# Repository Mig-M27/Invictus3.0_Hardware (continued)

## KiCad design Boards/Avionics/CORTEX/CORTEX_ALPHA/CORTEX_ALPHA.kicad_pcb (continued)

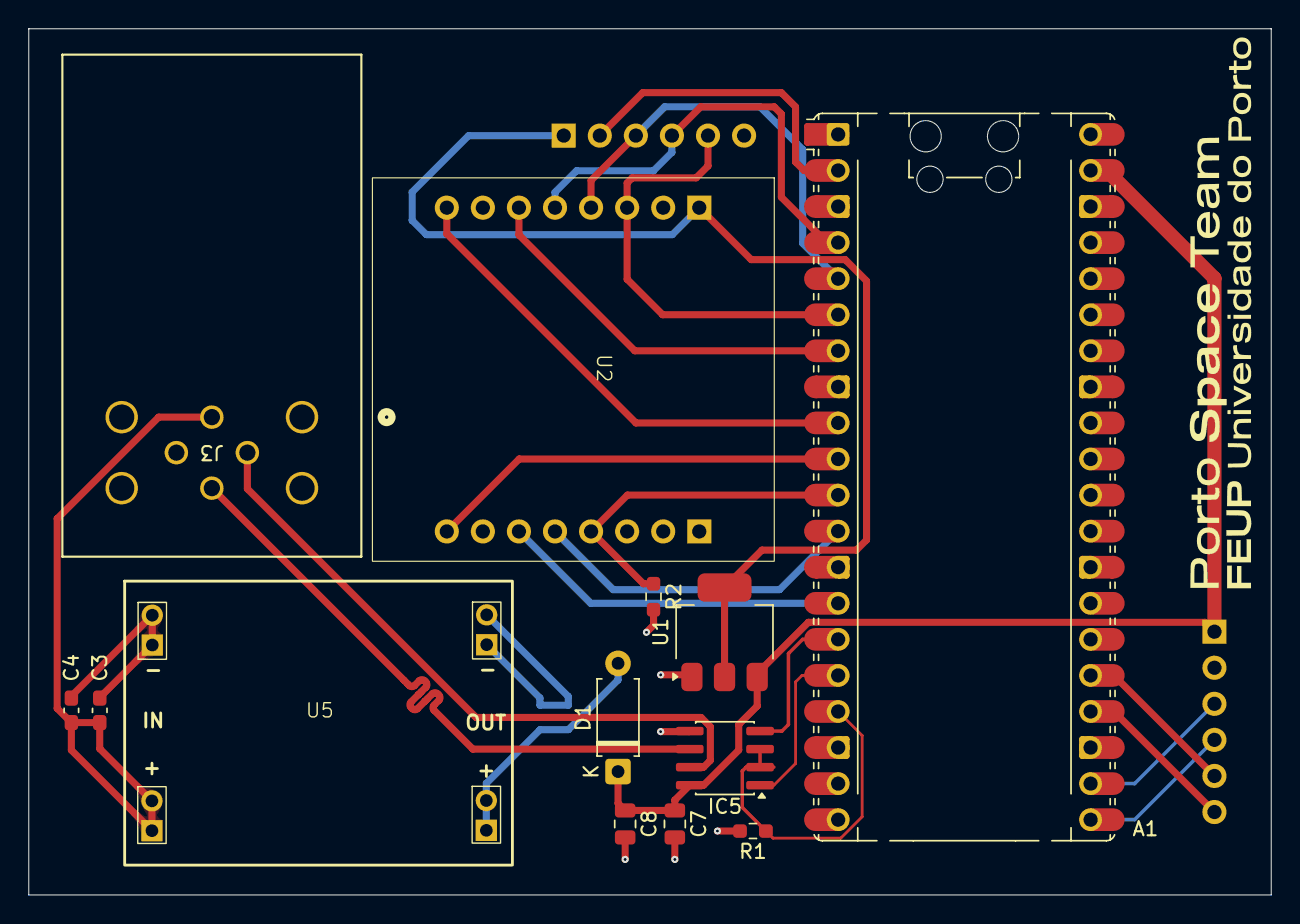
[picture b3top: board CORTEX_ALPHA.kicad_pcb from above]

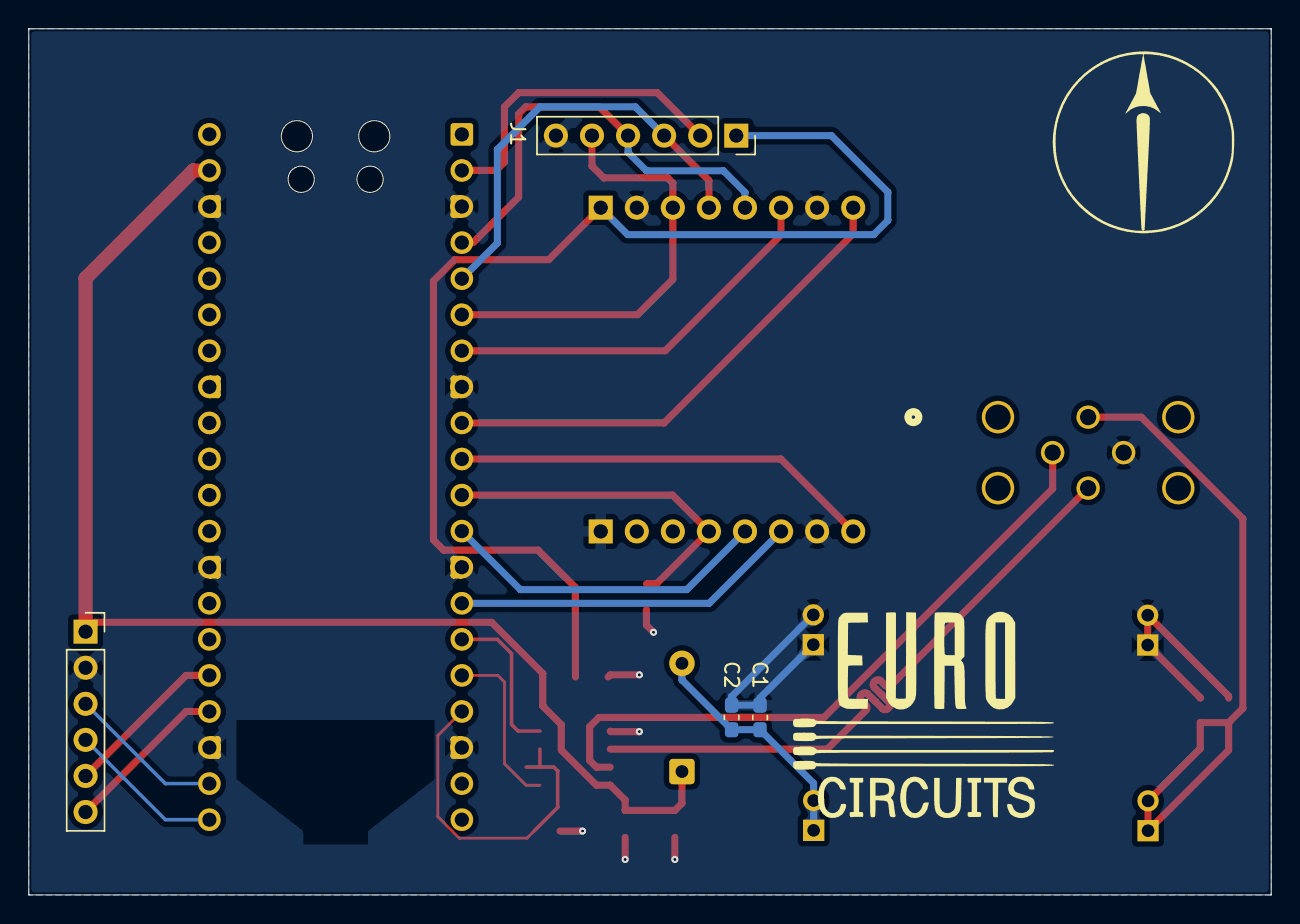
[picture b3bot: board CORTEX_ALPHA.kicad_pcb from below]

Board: 2 copper layers, 87.5 x 61.0 mm, 17 parts (4 on the bottom side), 24 nets.

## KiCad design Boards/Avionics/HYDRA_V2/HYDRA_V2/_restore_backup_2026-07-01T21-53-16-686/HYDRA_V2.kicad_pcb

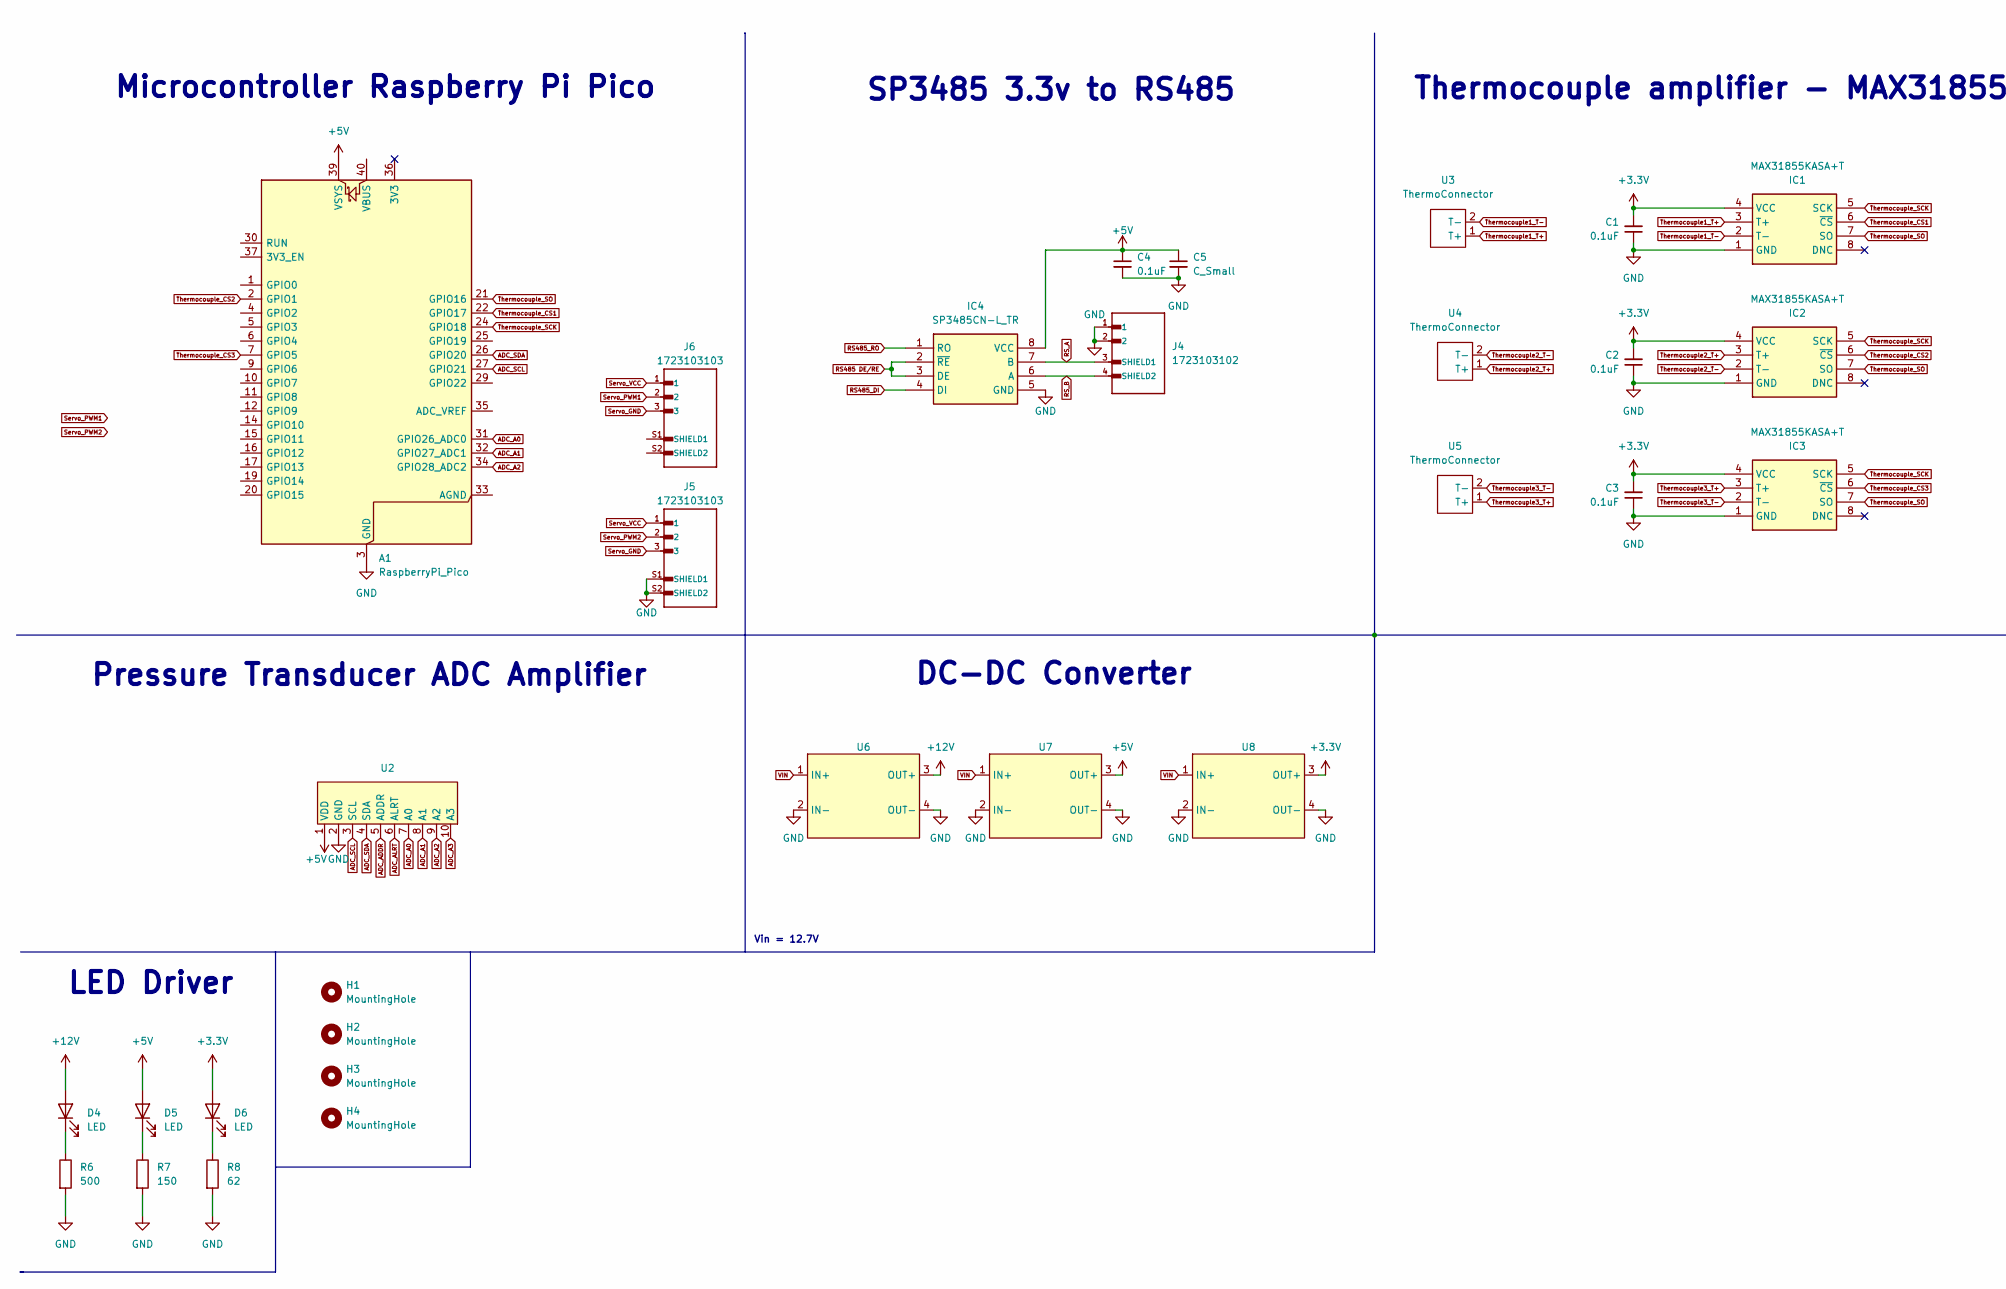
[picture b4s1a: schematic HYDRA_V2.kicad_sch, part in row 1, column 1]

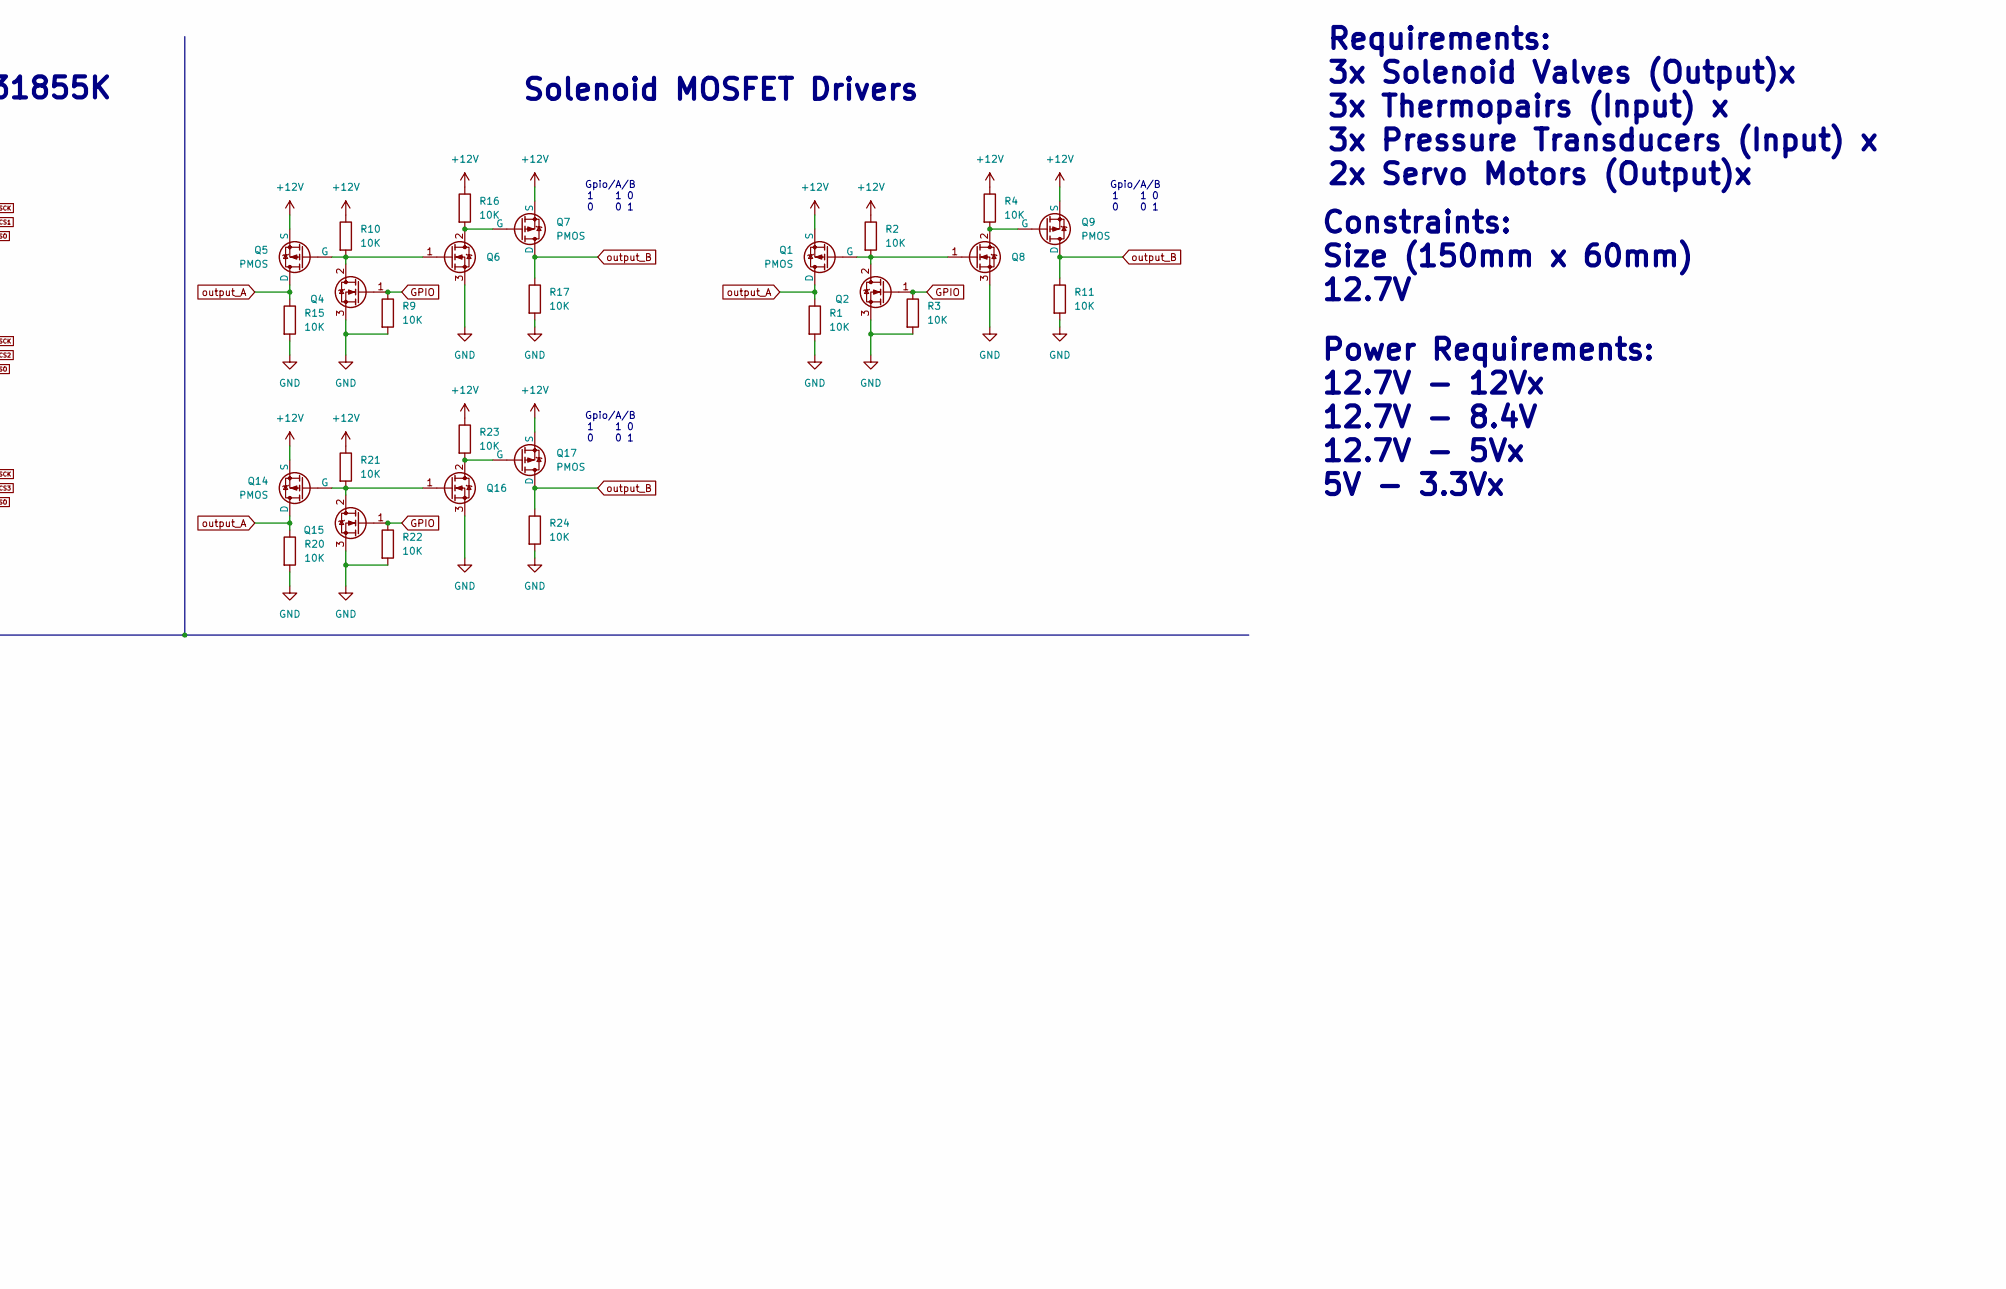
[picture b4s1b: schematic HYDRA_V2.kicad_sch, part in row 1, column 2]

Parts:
A1: RaspberryPi_Pico; RaspberryPi_Pico_Common_Unspecified
C1, C2, C3, C4: 0.1uF; C_0805_2012Metric
C5: C_Small; C_0805_2012Metric
D4, D5, D6: LED; LED_D3.0mm
H1, H2, H3, H4: MountingHole; MountingHole_3.2mm_M3_ISO7380
IC1, IC2, IC3: MAX31855KASA+T; SOIC127P600X175-8N; Mouser Part Number 700-MAX31855KASA+T
IC4: SP3485CN-L_TR; SOIC127P600X175-8N; Mouser Part Number 701-SP3485CN-L/TR
J4: 1723103102; CONN02_1723103102_MOL; MANUFACTURER_PART_NUMBER 1723103102; DigiKey_Part_Number 900-1723103102-ND
J5, J6: 1723103103; MOLEX_1723103103; PARTREV B1; DigiKey_Part_Number 900-1723103103-ND
Q1, Q5, Q7, Q9, Q14, Q17: PMOS; TO-220-3_Vertical
Q2, Q4, Q6, Q8, Q15, Q16: IRLB3813PBF-ND; TO-220-3_Vertical
R1, R2, R3, R4, R9, R10, R11, R15, R16, R17, R20, R21, R22, R23, R24: 10K; R_0805_2012Metric_Pad1.20x1.40mm_HandSolder
R6: 500; R_0805_2012Metric
R7: 150; R_0805_2012Metric
R8: 62; R_0805_2012Metric
U2: Pressure_Amp
U3, U4, U5: ThermoConnector; Thermo Type K PCB Connector
U6, U7, U8: DCDC_Module

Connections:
+3.3V: C1.2, C2.2, C3.2, D6.2 (A), IC1.4 (VCC), IC2.4 (VCC), IC3.4 (VCC), U8.3 (OUT+)
+5V: A1.39 (VSYS), C4.1, C5.1, D5.2 (A), IC4.8 (VCC), U2.1 (VDD), U7.3 (OUT+)
+12V: D4.2 (A), Q1.3 (S), Q5.3 (S), Q7.3 (S), Q9.3 (S), Q14.3 (S), Q17.3 (S), R2.1, R4.1, R10.1, R16.1, R21.1, R23.1, U6.3 (OUT+)
ADC_A0: A1.31 (GPIO26_ADC0), U2.7 (A0)
ADC_A1: A1.32 (GPIO27_ADC1), U2.8 (A1)
ADC_A2: A1.34 (GPIO28_ADC2), U2.9 (A2)
ADC_A3: U2.10 (A3)
ADC_ADDR: U2.5 (ADDR)
ADC_ALRT: U2.6 (ALRT)
ADC_SCL: A1.27 (GPIO21), U2.3 (SCL)
ADC_SDA: A1.26 (GPIO20), U2.4 (SDA)
GND: A1.3 (GND), A1.8 (GND), A1.13 (GND), A1.18 (GND), A1.23 (GND), A1.28 (GND), A1.38 (GND), C1.1, C2.1, C3.1, C4.2, C5.2, IC1.1 (GND), IC2.1 (GND), IC3.1 (GND), IC4.5 (GND), J4.1, J4.2, J5.S1 (SHIELD1), J5.S2 (SHIELD2), Q2.3 (S), Q4.3 (S), Q6.3 (S), Q8.3 (S), Q15.3 (S), Q16.3 (S), R1.2, R3.2, R6.2, R7.2, R8.2, R9.2, R11.2, R15.2, R17.2, R20.2, R22.2, R24.2, U2.2 (GND), U6.2 (IN-), U6.4 (OUT-), U7.2 (IN-), U7.4 (OUT-), U8.2 (IN-), U8.4 (OUT-)
GPIO: Q2.1 (G), Q4.1 (G), Q15.1 (G), R3.1, R9.1, R22.1
unnamed: D4.1 (K), R6.1
unnamed: D5.1 (K), R7.1
unnamed: D6.1 (K), R8.1
unnamed: Q1.2 (G), Q2.2 (D), Q8.1 (G), R2.2
unnamed: Q4.2 (D), Q5.2 (G), Q6.1 (G), R10.2
unnamed: Q6.2 (D), Q7.2 (G), R16.2
unnamed: Q8.2 (D), Q9.2 (G), R4.2
unnamed: Q14.2 (G), Q15.2 (D), Q16.1 (G), R21.2
unnamed: Q16.2 (D), Q17.2 (G), R23.2
RS485 DE/RE: IC4.2 (~RE), IC4.3 (DE)
RS485_DI: IC4.4 (DI)
RS485_RO: IC4.1 (RO)
RS_A: IC4.7 (B), J4.3 (SHIELD1)
RS_B: IC4.6 (A), J4.4 (SHIELD2)
Servo_GND: J5.3, J6.3
Servo_PWM1: J6.2
Servo_PWM2: J5.2
Servo_VCC: J5.1, J6.1
Thermocouple1_T+: IC1.3 (T+), U3.1 (T+)
Thermocouple1_T-: IC1.2 (T-), U3.2 (T-)
Thermocouple2_T+: IC2.3 (T+), U4.1 (T+)
Thermocouple2_T-: IC2.2 (T-), U4.2 (T-)
Thermocouple3_T+: IC3.3 (T+), U5.1 (T+)
Thermocouple3_T-: IC3.2 (T-), U5.2 (T-)
Thermocouple_CS1: A1.22 (GPIO17), IC1.6 (~CS)
Thermocouple_CS2: A1.2 (GPIO1), IC2.6 (~CS)
Thermocouple_CS3: A1.7 (GPIO5), IC3.6 (~CS)
Thermocouple_SCK: A1.24 (GPIO18), IC1.5 (SCK), IC2.5 (SCK), IC3.5 (SCK)
Thermocouple_SO: A1.21 (GPIO16), IC1.7 (SO), IC2.7 (SO), IC3.7 (SO)
VIN: U6.1 (IN+), U7.1 (IN+), U8.1 (IN+)
output_A: Q1.1 (D), Q5.1 (D), Q14.1 (D), R1.1, R15.1, R20.1
output_B: Q7.1 (D), Q9.1 (D), Q17.1 (D), R11.1, R17.1, R24.1

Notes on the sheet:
Pressure Transducer ADC Amplifier
Requirements: 3x Solenoid Valves (Output)x 3x Thermopairs (Input) x 3x Pressure Transducers (Input) x 2x Servo Motors (Output)x
Thermocouple amplifier - MAX31855K
DC-DC Converter
LED Driver
Gpio/A/B 1 1 0 0 0 1
Constraints: Size (150mm x 60mm) 12.7V
Vin = 12.7V
Microcontroller Raspberry Pi Pico
SP3485 3.3v to RS485
Solenoid MOSFET Drivers
Power Requirements: 12.7V - 12Vx 12.7V - 8.4V 12.7V - 5Vx 5V - 3.3Vx

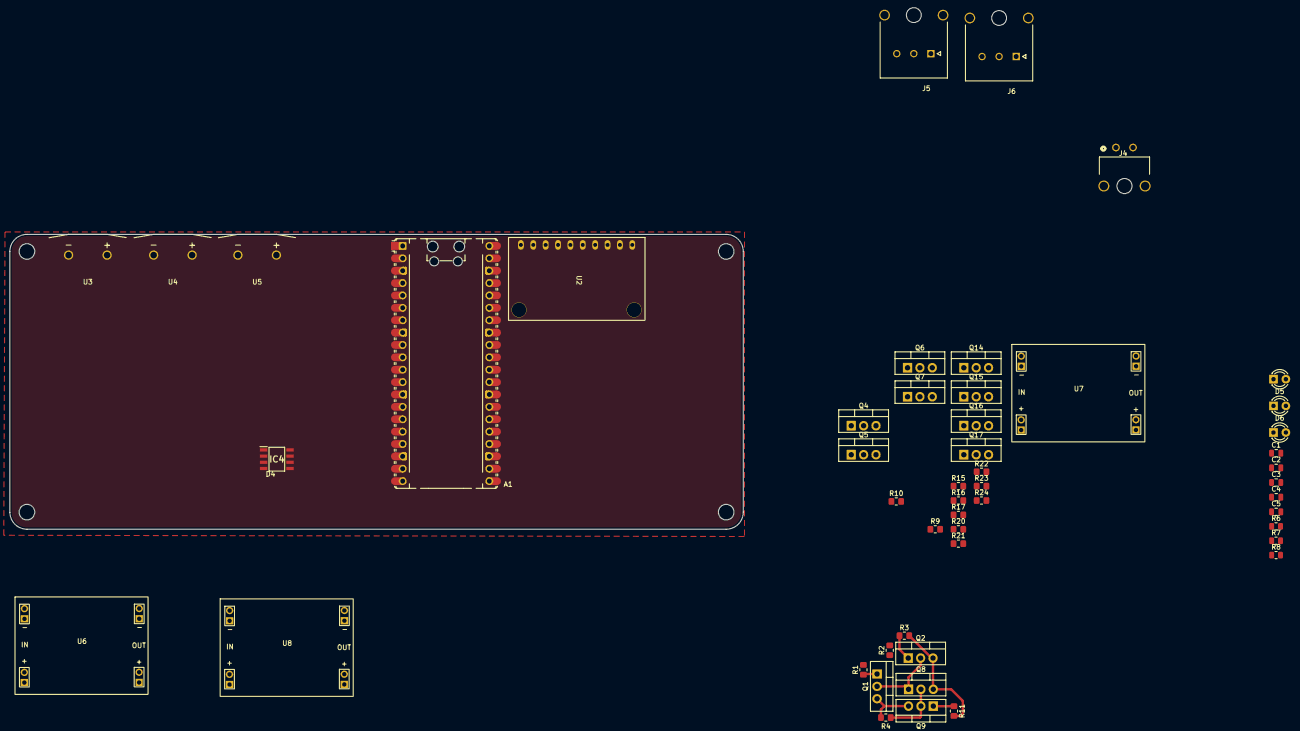
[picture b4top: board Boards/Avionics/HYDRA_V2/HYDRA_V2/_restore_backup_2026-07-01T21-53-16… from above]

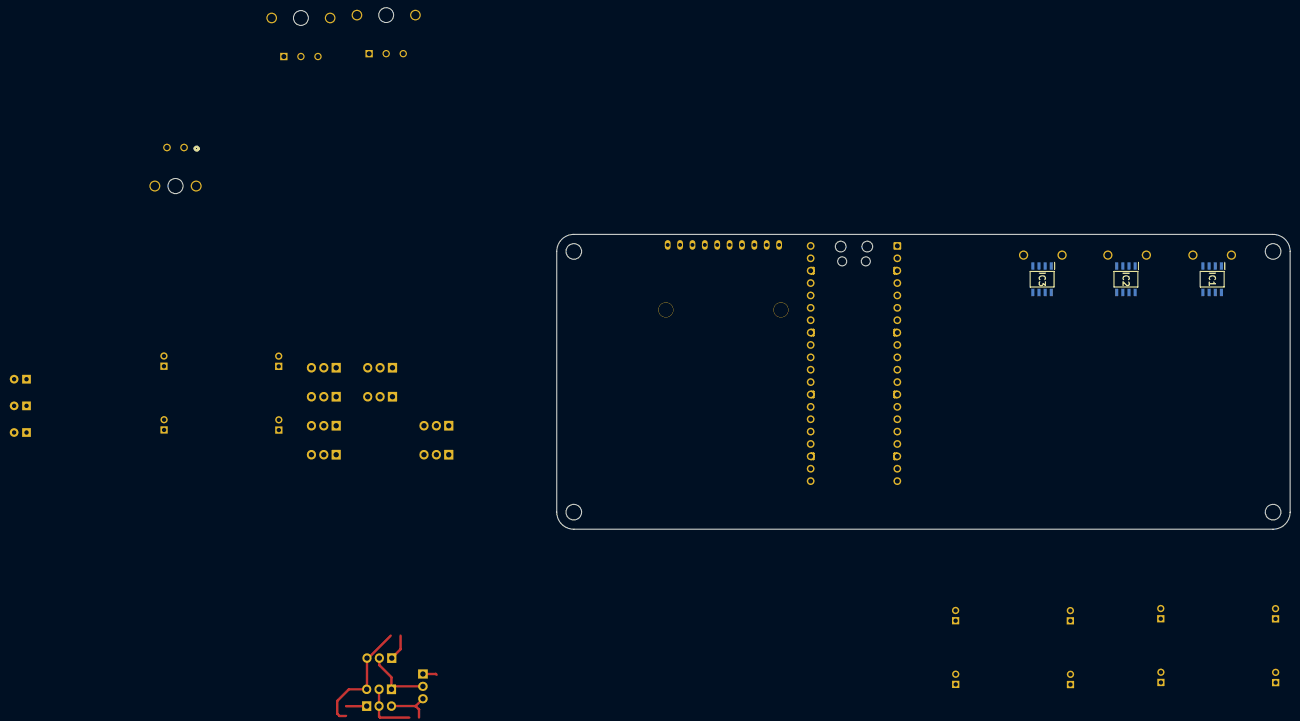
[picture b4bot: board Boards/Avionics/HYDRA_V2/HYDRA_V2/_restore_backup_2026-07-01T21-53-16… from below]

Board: 4 copper layers, 150.5 x 60.5 mm, 57 parts (3 on the bottom side), 38 nets.

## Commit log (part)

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2026-06-22 Hydra V2
